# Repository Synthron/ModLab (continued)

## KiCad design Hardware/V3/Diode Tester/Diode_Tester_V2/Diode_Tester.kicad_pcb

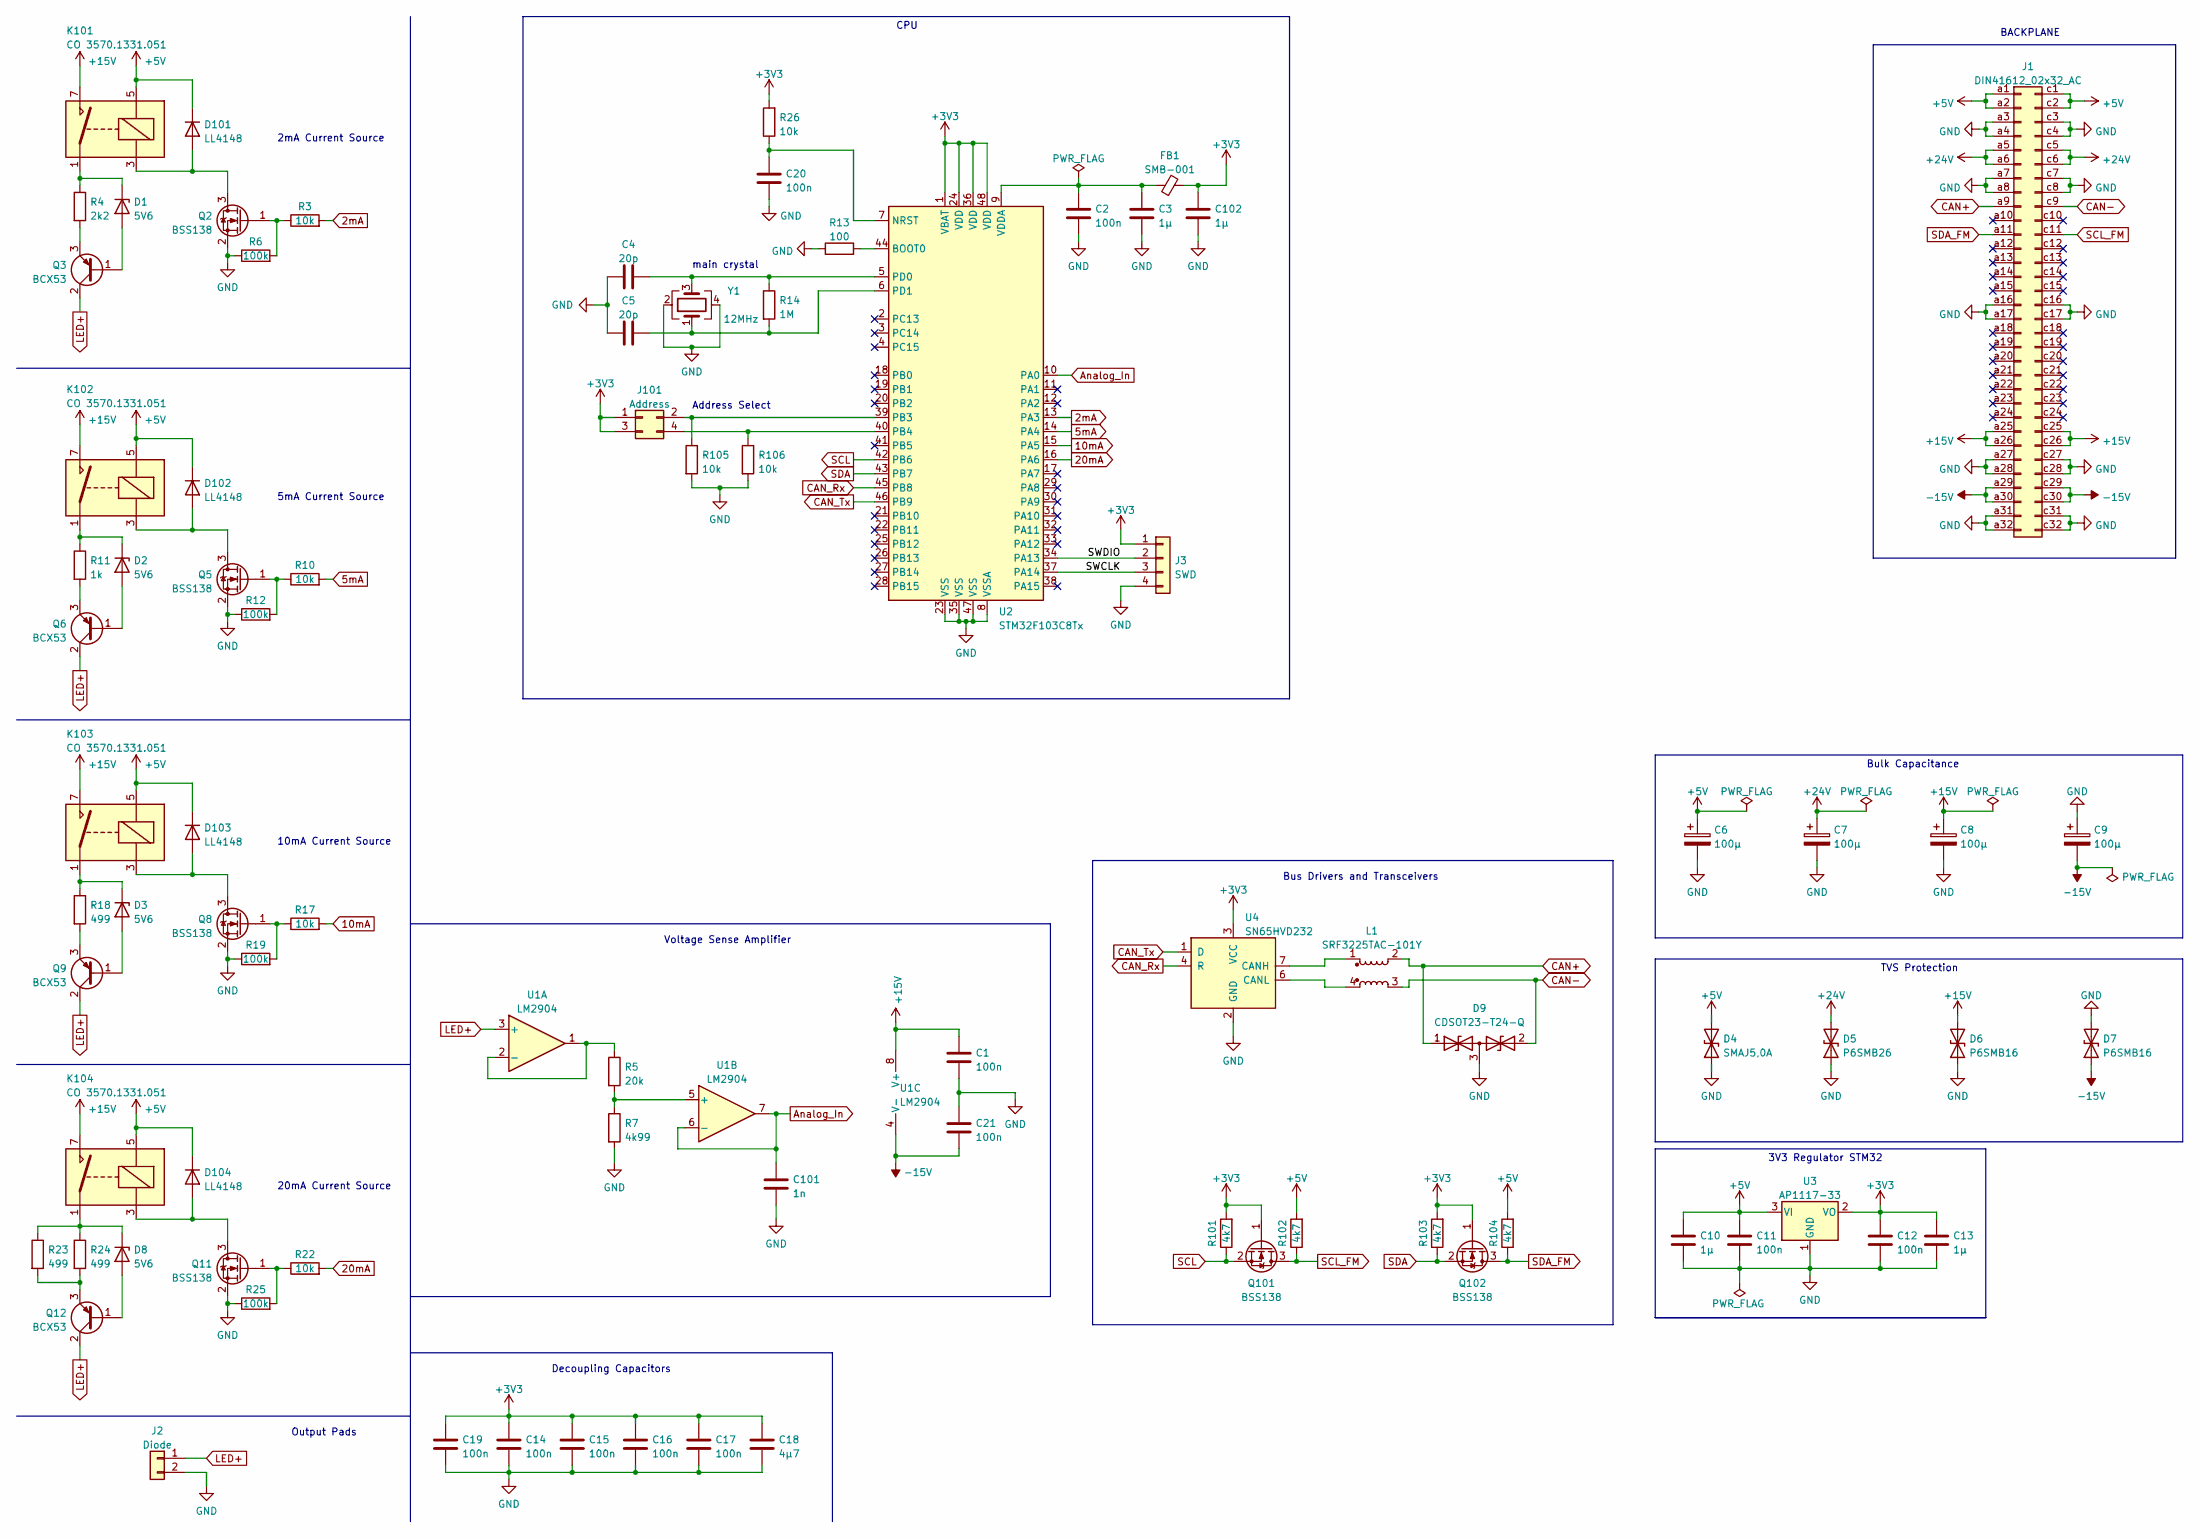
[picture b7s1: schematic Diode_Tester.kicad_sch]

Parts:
C1, C2, C11, C12, C14, C15, C16, C17, C19, C20, C21: 100n; C_0805_2012Metric
C3, C10, C13, C102: 1µ; C_0805_2012Metric
C4, C5: 20p; C_0805_2012Metric
C6, C7, C8, C9: 100µ; CP_Radial_D8.0mm_P5.00mm
C18: 4µ7; C_0805_2012Metric
C101: 1n; C_0805_2012Metric
D1, D2, D3, D8: 5V6; D_MiniMELF
D4: SMAJ5,0A; D_SMA
D5: P6SMB26; D_SMA
D6, D7: P6SMB16; D_SMA
D9: CDSOT23-T24-Q; SOT-23
D101, D102, D103, D104: LL4148; D_MiniMELF
FB1: SMB-001
J1: DIN41612_02x32_AC; VG64_Euro
J2: Diode; PinHeader_1x02_P2.54mm_Vertical
J3: SWD; JST_XH_B4B-XH-A_1x04_P2.50mm_Vertical
J101: Address; PinHeader_2x02_P2.54mm_Vertical
K101, K102, K103, K104: CO 3570.1331.051; Relay_SPST_StandexMeder_SIL_Form1A
L1: SRF3225TAC-101Y; SRF3225TAC
Q2, Q5, Q8, Q11, Q101, Q102: BSS138; SOT-23
Q3, Q6, Q9, Q12: BCX53; SOT-89-3
R3, R10, R17, R22, R26, R105, R106: 10k; R_0805_2012Metric
R4: 2k2; R_0805_2012Metric
R5: 20k; R_0805_2012Metric
R6, R12, R19, R25: 100k; R_0805_2012Metric
R7: 4k99; R_0805_2012Metric
R11: 1k; R_0805_2012Metric
R13: 100; R_0805_2012Metric
R14: 1M; R_0805_2012Metric
R18, R23, R24: 499; R_0805_2012Metric
R101, R102, R103, R104: 4k7; R_0805_2012Metric
U1: LM2904; SOIC-8_3.9x4.9mm_P1.27mm
U2: STM32F103C8Tx; LQFP-48_7x7mm_P0.5mm
U3: AP1117-33; SOT-223-3_TabPin2
U4: SN65HVD232; SOIC-8_3.9x4.9mm_P1.27mm
Y1: 12MHz; Crystal_SMD_5032-4Pin_5.0x3.2mm

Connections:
2mA: R3.2, U2.13 (PA3)
5mA: R10.2, U2.14 (PA4)
10mA: R17.2, U2.15 (PA5)
20mA: R22.2, U2.16 (PA6)
+3V3: C12.1, C13.1, C14.1, C15.1, C16.1, C17.1, C18.1, C19.1, C102.1, FB1.2, J3.1, J101.1, J101.3, Q101.1 (G), Q102.1 (G), R26.2, R101.2, R103.2, U2.1 (VBAT), U2.24 (VDD), U2.36 (VDD), U2.48 (VDD), U3.2 (VO), U4.3 (VCC)
+5V: C6.1, C10.1, C11.1, D4.2 (A2), D101.1 (K), D102.1 (K), D103.1 (K), D104.1 (K), J1.a1, J1.a2, J1.c1, J1.c2, K101.5, K102.5, K103.5, K104.5, R102.2, R104.2, U3.3 (VI)
+15V: C1.1, C8.1, D6.2 (A2), J1.a25, J1.a26, J1.c25, J1.c26, K101.7, K102.7, K103.7, K104.7, U1.8 (V+)
+24V: C7.1, D5.2 (A2), J1.a5, J1.a6, J1.c5, J1.c6
-15V: C9.2, C21.2, D7.1 (A1), J1.a29, J1.a30, J1.c29, J1.c30, U1.4 (V-)
/SWCLK: J3.3, U2.37 (PA14)
/SWDIO: J3.2, U2.34 (PA13)
Analog_In: C101.1, U1.6 (-), U1.7, U2.10 (PA0)
CAN+: D9.1 (A1), J1.a9, L1.2
CAN-: D9.2 (A2), J1.c9, L1.3
CAN_Rx: U2.45 (PB8), U4.4 (R)
CAN_Tx: U2.46 (PB9), U4.1 (D)
GND: C1.2, C2.2, C3.2, C4.1, C5.1, C6.2, C7.2, C8.2, C9.1, C10.2, C11.2, C12.2, C13.2, C14.2, C15.2, C16.2, C17.2, C18.2, C19.2, C20.2, C21.1, C101.2, C102.2, D4.1 (A1), D5.1 (A1), D6.1 (A1), D7.2 (A2), D9.3 (common), J1.a3, J1.a4, J1.a7, J1.a8, J1.a16, J1.a17, J1.a27, J1.a28, J1.a31, J1.a32, J1.c3, J1.c4, J1.c7, J1.c8, J1.c16, J1.c17, J1.c27, J1.c28, J1.c31, J1.c32, J2.2, J3.4, Q2.2 (S), Q5.2 (S), Q8.2 (S), Q11.2 (S), R6.1, R7.2, R12.1, R13.1, R19.1, R25.1, R105.2, R106.2, U2.8 (VSSA), U2.23 (VSS), U2.35 (VSS), U2.47 (VSS), U3.1 (GND), U4.2 (GND), Y1.2, Y1.4
LED+: J2.1, Q3.2 (C), Q6.2 (C), Q9.2 (C), Q12.2 (C), U1.3 (+)
unnamed: C2.1, C3.1, FB1.1, U2.9 (VDDA)
unnamed: C4.2, R14.1, U2.5 (PD0), Y1.3
unnamed: C5.2, R14.2, U2.6 (PD1), Y1.1
unnamed: C20.1, R26.1, U2.7 (NRST)
unnamed: D1.1 (K), K101.1, R4.1
unnamed: D1.2 (A), Q3.1 (B)
unnamed: D2.1 (K), K102.1, R11.1
unnamed: D2.2 (A), Q6.1 (B)
unnamed: D3.1 (K), K103.1, R18.1
unnamed: D3.2 (A), Q9.1 (B)
unnamed: D8.1 (K), K104.1, R23.1, R24.1
unnamed: D8.2 (A), Q12.1 (B)
unnamed: L1.1, U4.7 (CANH)
unnamed: L1.4, U4.6 (CANL)
unnamed: Q2.1 (G), R3.1, R6.2
unnamed: D101.2 (A), K101.3, Q2.3 (D)
unnamed: Q3.3 (E), R4.2
unnamed: Q5.1 (G), R10.1, R12.2
unnamed: D102.2 (A), K102.3, Q5.3 (D)
unnamed: Q6.3 (E), R11.2
unnamed: Q8.1 (G), R17.1, R19.2
unnamed: D103.2 (A), K103.3, Q8.3 (D)
unnamed: Q9.3 (E), R18.2
unnamed: Q11.1 (G), R22.1, R25.2
unnamed: D104.2 (A), K104.3, Q11.3 (D)
unnamed: Q12.3 (E), R23.2, R24.2
unnamed: R5.1, U1.1, U1.2 (-)
unnamed: R5.2, R7.1, U1.5 (+)
unnamed: R13.2, U2.44 (BOOT0)
unnamed: J101.2, R105.1, U2.39 (PB3)
unnamed: J101.4, R106.1, U2.40 (PB4)
SCL: Q101.2 (S), R101.1, U2.42 (PB6)
SCL_FM: J1.c11, Q101.3 (D), R102.1
SDA: Q102.2 (S), R103.1, U2.43 (PB7)
SDA_FM: J1.a11, Q102.3 (D), R104.1

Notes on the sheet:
2mA Current Source
10mA Current Source
Decoupling Capacitors
TVS Protection
3V3 Regulator STM32
Output Pads
main crystal
20mA Current Source
Address Select
CPU
BACKPLANE
Bus Drivers and Transceivers
Bulk Capacitance
5mA Current Source
Voltage Sense Amplifier

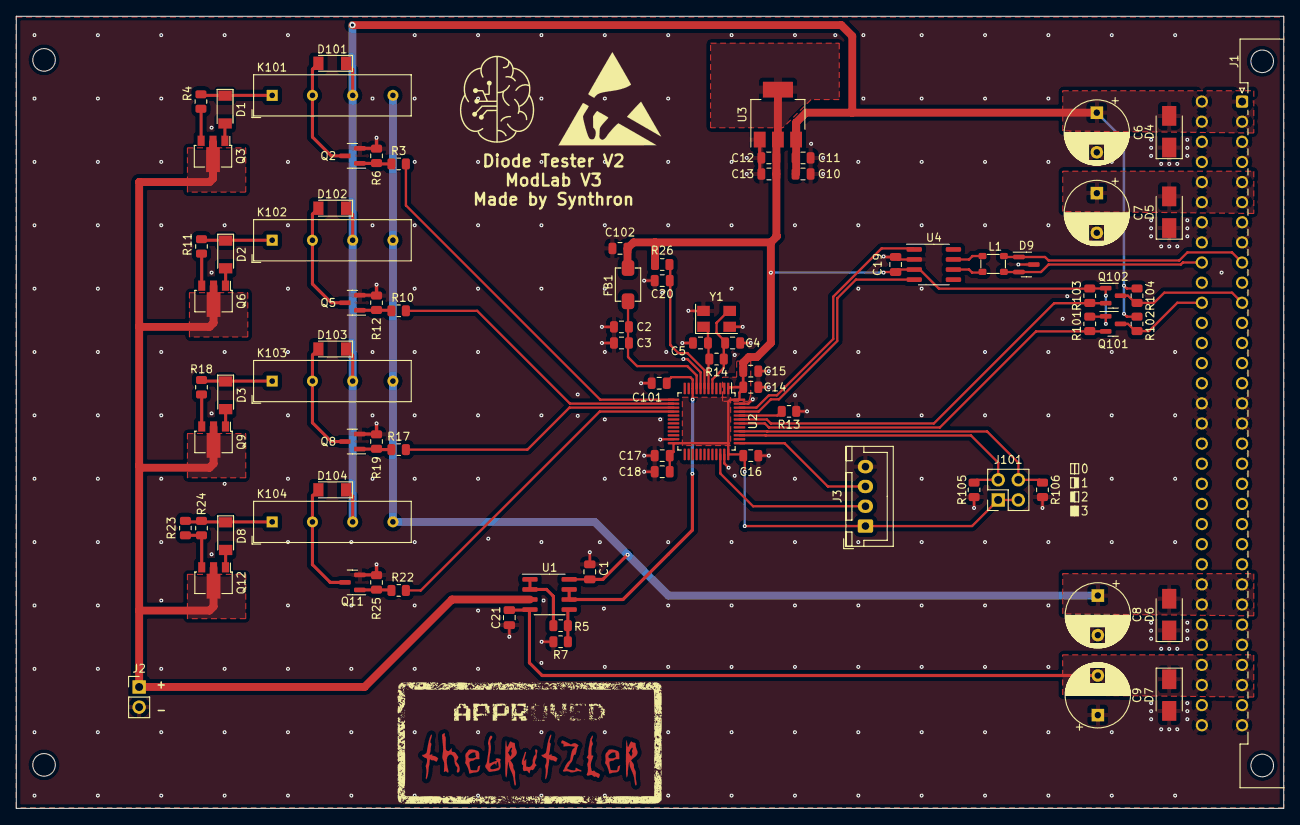
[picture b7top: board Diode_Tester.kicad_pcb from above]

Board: 2 copper layers, 160.0 x 100.0 mm, 85 parts (0 on the bottom side), 53 nets.

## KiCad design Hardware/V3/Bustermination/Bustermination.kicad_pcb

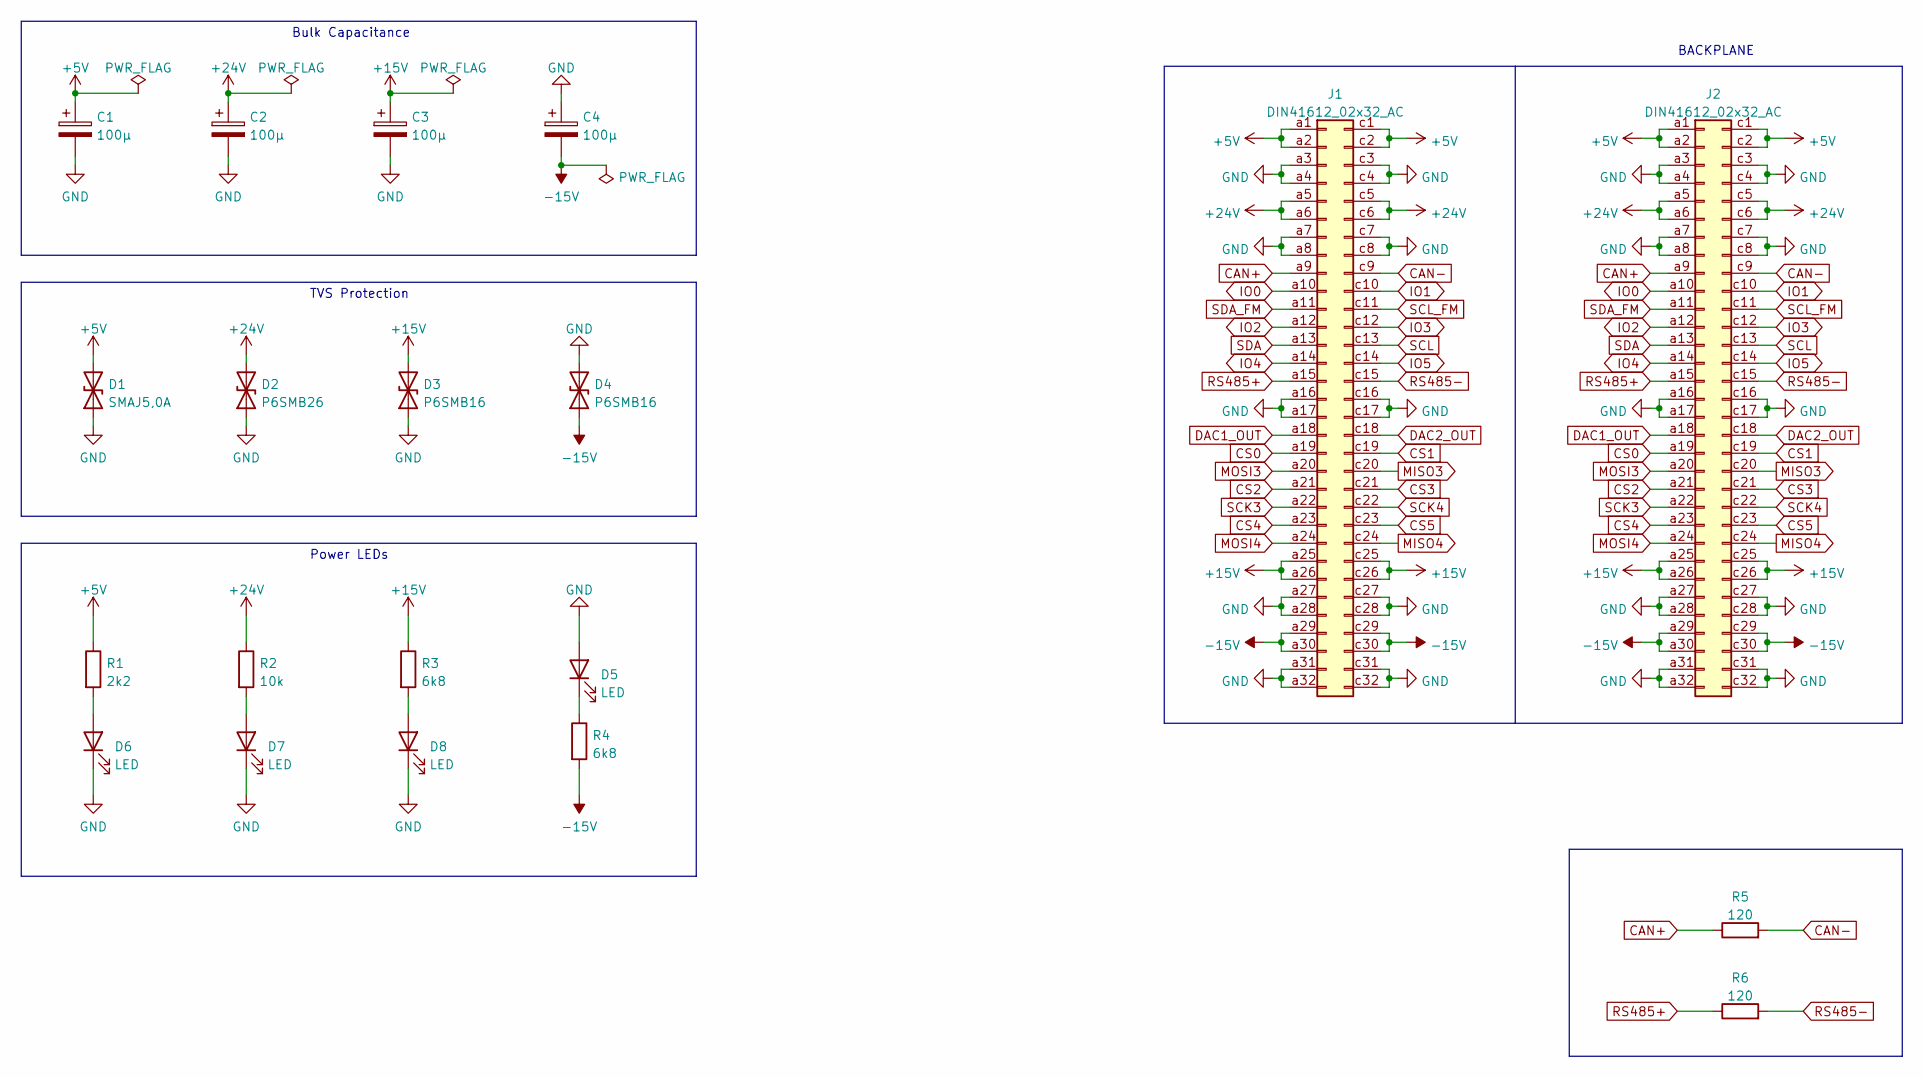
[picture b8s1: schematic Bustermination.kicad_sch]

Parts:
C1, C2, C3, C4: 100µ; CP_Radial_D8.0mm_P5.00mm
D1: SMAJ5,0A; D_SMA
D2: P6SMB26; D_SMA
D3, D4: P6SMB16; D_SMA
D5, D6, D7, D8: LED; LED_D3.0mm
J1: DIN41612_02x32_AC; DIN41612_C_2x32_Female_Vertical_THT
J2: DIN41612_02x32_AC; VG64_Euro
R1: 2k2; R_Axial_DIN0204_L3.6mm_D1.6mm_P7.62mm_Horizontal
R2: 10k; R_Axial_DIN0204_L3.6mm_D1.6mm_P7.62mm_Horizontal
R3, R4: 6k8; R_Axial_DIN0204_L3.6mm_D1.6mm_P7.62mm_Horizontal
R5, R6: 120; R_Axial_DIN0204_L3.6mm_D1.6mm_P7.62mm_Horizontal

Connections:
+5V: C1.1, D1.2 (A2), J1.a1, J1.a2, J1.c1, J1.c2, J2.a1, J2.a2, J2.c1, J2.c2, R1.1
+15V: C3.1, D3.2 (A2), J1.a25, J1.a26, J1.c25, J1.c26, J2.a25, J2.a26, J2.c25, J2.c26, R3.1
+24V: C2.1, D2.2 (A2), J1.a5, J1.a6, J1.c5, J1.c6, J2.a5, J2.a6, J2.c5, J2.c6, R2.1
-15V: C4.2, D4.1 (A1), J1.a29, J1.a30, J1.c29, J1.c30, J2.a29, J2.a30, J2.c29, J2.c30, R4.2
CAN+: J1.a9, J2.a9, R5.1
CAN-: J1.c9, J2.c9, R5.2
CS0: J1.a19, J2.a19
CS1: J1.c19, J2.c19
CS2: J1.a21, J2.a21
CS3: J1.c21, J2.c21
CS4: J1.a23, J2.a23
CS5: J1.c23, J2.c23
DAC1_OUT: J1.a18, J2.a18
DAC2_OUT: J1.c18, J2.c18
GND: C1.2, C2.2, C3.2, C4.1, D1.1 (A1), D2.1 (A1), D3.1 (A1), D4.2 (A2), D5.2 (A), D6.1 (K), D7.1 (K), D8.1 (K), J1.a3, J1.a4, J1.a7, J1.a8, J1.a16, J1.a17, J1.a27, J1.a28, J1.a31, J1.a32, J1.c3, J1.c4, J1.c7, J1.c8, J1.c16, J1.c17, J1.c27, J1.c28, J1.c31, J1.c32, J2.a3, J2.a4, J2.a7, J2.a8, J2.a16, J2.a17, J2.a27, J2.a28, J2.a31, J2.a32, J2.c3, J2.c4, J2.c7, J2.c8, J2.c16, J2.c17, J2.c27, J2.c28, J2.c31, J2.c32
IO0: J1.a10, J2.a10
IO1: J1.c10, J2.c10
IO2: J1.a12, J2.a12
IO3: J1.c12, J2.c12
IO4: J1.a14, J2.a14
IO5: J1.c14, J2.c14
MISO3: J1.c20, J2.c20
MISO4: J1.c24, J2.c24
MOSI3: J1.a20, J2.a20
MOSI4: J1.a24, J2.a24
unnamed: D5.1 (K), R4.1
unnamed: D6.2 (A), R1.2
unnamed: D7.2 (A), R2.2
unnamed: D8.2 (A), R3.2
RS485+: J1.a15, J2.a15, R6.1
RS485-: J1.c15, J2.c15, R6.2
SCK3: J1.a22, J2.a22
SCK4: J1.c22, J2.c22
SCL: J1.c13, J2.c13
SCL_FM: J1.c11, J2.c11
SDA: J1.a13, J2.a13
SDA_FM: J1.a11, J2.a11

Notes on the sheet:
TVS Protection
Power LEDs
BACKPLANE
Bulk Capacitance

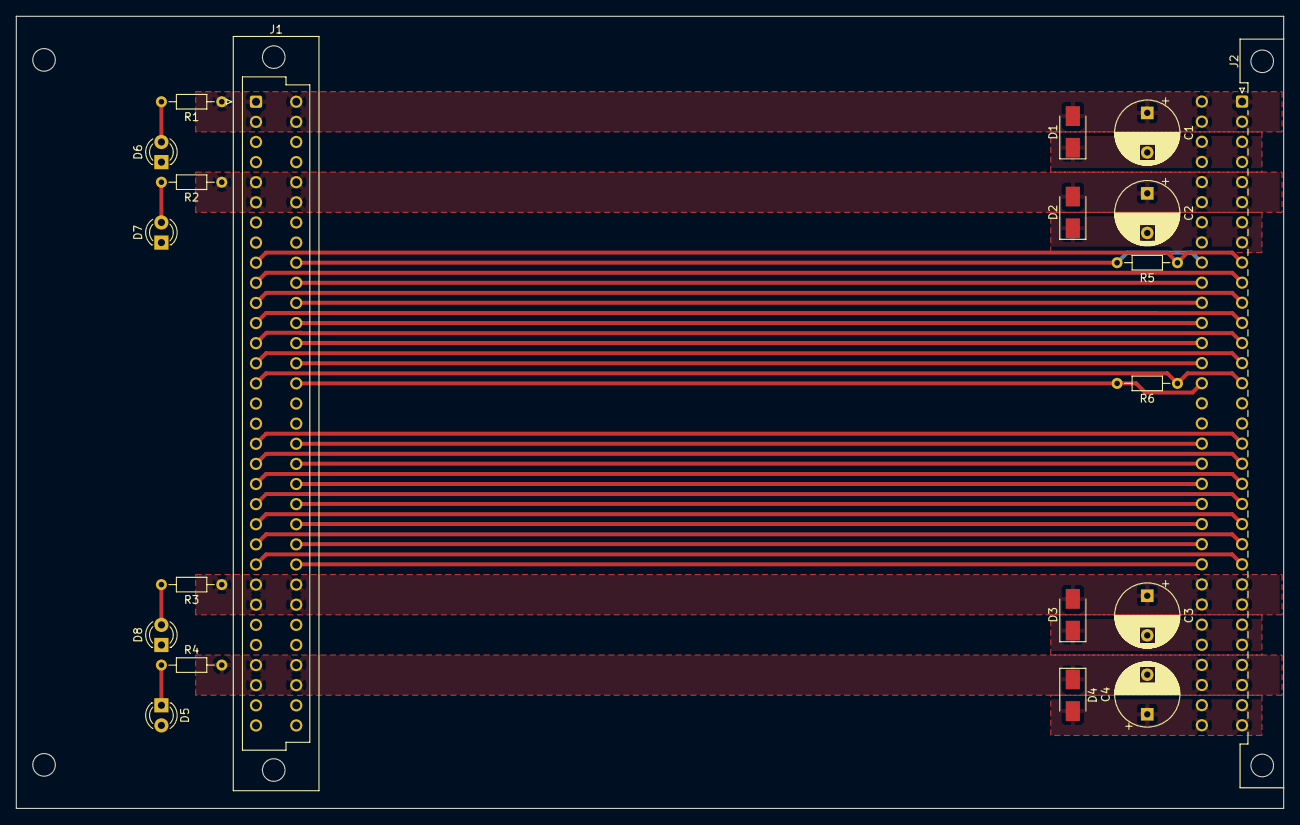
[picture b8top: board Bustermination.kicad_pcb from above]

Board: 2 copper layers, 160.0 x 100.0 mm, 20 parts (0 on the bottom side), 37 nets.

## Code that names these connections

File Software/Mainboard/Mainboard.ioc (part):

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Mcu.Name=STM32F407V(E-G)Tx
Mcu.Package=LQFP100
Mcu.UserName=STM32F407VGTx
PA0-WKUP.Mode=Asynchronous
PA0-WKUP.Signal=UART4_TX
PA1.Mode=Asynchronous
PA1.Signal=UART4_RX
PA10.GPIOParameters=GPIO_Label
PA10.GPIO_Label=USB_Disconnect
PA10.Signal=GPIO_Output
PA11.Mode=Device_Only
PA11.Signal=USB_OTG_FS_DM
PA12.Mode=Device_Only
PA12.Signal=USB_OTG_FS_DP
PA13.Mode=Serial_Wire
PA13.Signal=SYS_JTMS-SWDIO
PA14.Mode=Serial_Wire
PA14.Signal=SYS_JTCK-SWCLK
PA2.GPIOParameters=GPIO_Label
PA2.GPIO_Label=RS485_DIR
PA2.Signal=GPIO_Output
PA3.GPIOParameters=GPIO_Label
PA3.GPIO_Label=ESP_CS
PA3.Signal=GPIO_Output
PA4.Signal=COMP_DAC1_group
PA5.Signal=COMP_DAC2_group
PA6.Mode=Full_Duplex_Master
PA6.Signal=SPI1_MISO
PA7.Mode=Full_Duplex_Master
PA7.Signal=SPI1_MOSI
PA9.Mode=Asynchronous
PA9.Signal=USART1_TX
PB0.GPIOParameters=GPIO_Label
PB0.GPIO_Label=SD_DETECT
PB0.Signal=GPIO_Input
PB1.GPIOParameters=GPIO_Label
PB1.GPIO_Label=SD_PROTECT
PB1.Signal=GPIO_Input
PB10.Mode=I2C
PB10.Signal=I2C2_SCL
PB11.Mode=I2C
PB11.Signal=I2C2_SDA
PB13.Mode=Full_Duplex_Master
PB13.Signal=SPI2_SCK
PB3.Mode=Full_Duplex_Master
PB3.Signal=SPI1_SCK
PB5.Mode=Full_Duplex_Master
PB5.Signal=SPI3_MOSI
PB6.Mode=I2C
PB6.Signal=I2C1_SCL
PB7.Mode=Asynchronous
PB7.Signal=USART1_RX
PB9.Mode=I2C
PB9.Signal=I2C1_SDA
PC0.GPIOParameters=GPIO_Label
PC0.GPIO_Label=ESP_RDY
PC0.Signal=GPIO_Input
PC1.GPIOParameters=GPIO_Label
PC1.GPIO_Label=ESP_CS
PC1.Signal=GPIO_Output
PC10.Mode=Full_Duplex_Master
PC10.Signal=SPI3_SCK
PC11.Mode=Full_Duplex_Master
PC11.Signal=SPI3_MISO
PC12.Mode=SD_1_bit
PC12.Signal=SDIO_CK
PC14-OSC32_IN.Mode=LSE-External-Oscillator
PC14-OSC32_IN.Signal=RCC_OSC32_IN
PC15-OSC32_OUT.Mode=LSE-External-Oscillator
PC15-OSC32_OUT.Signal=RCC_OSC32_OUT
PC2.Mode=Full_Duplex_Master
PC2.Signal=SPI2_MISO
PC3.Mode=Full_Duplex_Master
PC3.Signal=SPI2_MOSI
PC8.Mode=SD_1_bit
PC8.Signal=SDIO_D0
PD0.Mode=CAN_Activate
PD0.Signal=CAN1_RX
PD1.Mode=CAN_Activate
PD1.Signal=CAN1_TX
PD10.GPIOParameters=GPIO_Label
PD10.GPIO_Label=IO_0
PD10.Signal=GPIO_Output
PD11.GPIOParameters=GPIO_Label
PD11.GPIO_Label=IO_1
PD11.Signal=GPIO_Output
PD12.GPIOParameters=GPIO_Label
PD12.GPIO_Label=IO_2
PD12.Signal=GPIO_Output
PD13.GPIOParameters=GPIO_Label
PD13.GPIO_Label=IO_3
PD13.Signal=GPIO_Output
PD14.GPIOParameters=GPIO_Label
PD14.GPIO_Label=IO_4
PD14.Signal=GPIO_Output
PD15.GPIOParameters=GPIO_Label
PD15.GPIO_Label=IO_5
PD15.Signal=GPIO_Output
PD2.Mode=SD_1_bit
PD2.Signal=SDIO_CMD
PE0.GPIOParameters=GPIO_Label
PE0.GPIO_Label=LED_USB
PE0.Signal=GPIO_Output
PE1.GPIOParameters=GPIO_Label
PE1.GPIO_Label=LED_ESP
PE1.Signal=GPIO_Output
PE10.GPIOParameters=GPIO_Label
PE10.GPIO_Label=CS0
PE10.Signal=GPIO_Output
PE11.GPIOParameters=GPIO_Label
PE11.GPIO_Label=CS1
PE11.Signal=GPIO_Output
PE12.GPIOParameters=GPIO_Label
PE12.GPIO_Label=CS2
PE12.Signal=GPIO_Output
PE13.GPIOParameters=GPIO_Label
PE13.GPIO_Label=CS3
PE13.Signal=GPIO_Output
PE14.GPIOParameters=GPIO_Label
PE14.GPIO_Label=CS4
PE14.Signal=GPIO_Output
PE15.GPIOParameters=GPIO_Label
PE15.GPIO_Label=CS5
PE15.Signal=GPIO_Output
PE2.GPIOParameters=GPIO_Label
PE2.GPIO_Label=LED_SPI
PE2.Signal=GPIO_Output
PE3.GPIOParameters=GPIO_Label
PE3.GPIO_Label=LED_I2C
PE3.Signal=GPIO_Output
PE4.GPIOParameters=GPIO_Label
PE4.GPIO_Label=LED_SD
PE4.Signal=GPIO_Output
PE5.GPIOParameters=GPIO_Label
PE5.GPIO_Label=LED_CAN
PE5.Signal=GPIO_Output
PE6.GPIOParameters=GPIO_Label
PE6.GPIO_Label=LED_TFT
PE6.Signal=GPIO_Output
PE7.GPIOParameters=GPIO_Label
PE7.GPIO_Label=LED_485
PE7.Signal=GPIO_Output
PH0-OSC_IN.Mode=HSE-External-Oscillator
PH0-OSC_IN.Signal=RCC_OSC_IN
PH1-OSC_OUT.Mode=HSE-External-Oscillator
PH1-OSC_OUT.Signal=RCC_OSC_OUT
RCC.HSE_VALUE=8000000
RCC.SYSCLKFreq_VALUE=168000000
RCC.SYSCLKSource=RCC_SYSCLKSOURCE_PLLCLK
board=custom

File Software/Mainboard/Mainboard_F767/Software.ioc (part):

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Mcu.Name=STM32F767ZITx
Mcu.Package=LQFP144
Mcu.UserName=STM32F767ZITx
PA0/WKUP.GPIOParameters=GPIO_Label
PA0/WKUP.GPIO_Label=SD_Detect
PA0/WKUP.Signal=GPIO_Input
PA1.GPIOParameters=GPIO_Label
PA1.GPIO_Label=SD_Protect
PA1.Signal=GPIO_Input
PA10.GPIOParameters=GPIO_Label
PA10.GPIO_Label=USB_Disconnect
PA10.Signal=GPIO_Output
PA11.Mode=Device_Only
PA11.Signal=USB_OTG_FS_DM
PA12.Mode=Device_Only
PA12.Signal=USB_OTG_FS_DP
PA13.Mode=Serial_Wire
PA13.Signal=SYS_JTMS-SWDIO
PA14.Mode=Serial_Wire
PA14.Signal=SYS_JTCK-SWCLK
PA15.GPIOParameters=GPIO_Label
PA15.GPIO_Label=CS_2
PA15.Signal=GPIO_Output
PA2.GPIOParameters=GPIO_Label
PA2.GPIO_Label=ESP_RDY
PA2.Signal=GPXTI2
PA3.GPIOParameters=GPIO_Label
PA3.GPIO_Label=ESP_CS
PA3.Signal=GPIO_Output
PA4.Signal=COMP_DAC1_group
PA5.Signal=COMP_DAC2_group
PA6.Mode=Full_Duplex_Master
PA6.Signal=SPI1_MISO
PA7.Mode=Full_Duplex_Master
PA7.Signal=SPI1_MOSI
PA8.GPIOParameters=GPIO_Label
PA8.GPIO_Label=CS_0
PA8.Signal=GPIO_Output
PA9.GPIOParameters=GPIO_Label
PA9.GPIO_Label=CS_1
PA9.Signal=GPIO_Output
PB0.GPIOParameters=GPIO_Label
PB0.GPIO_Label=CS_3
PB0.Signal=GPIO_Output
PB1.GPIOParameters=GPIO_Label
PB1.GPIO_Label=CS_4
PB1.Signal=GPIO_Output
PB10.Mode=I2C
PB10.Signal=I2C2_SCL
PB11.Mode=I2C
PB11.Signal=I2C2_SDA
PB12.GPIOParameters=GPIO_Label
PB12.GPIO_Label=GPIO_0
PB12.Signal=GPIO_Input
PB13.Mode=Full_Duplex_Master
PB13.Signal=SPI2_SCK
PB14.Mode=Asynchronous
PB14.Signal=USART1_TX
PB15.Mode=Asynchronous
PB15.Signal=USART1_RX
PB2.Mode=Full_Duplex_Master
PB2.Signal=SPI3_MOSI
PB3.Mode=Full_Duplex_Master
PB3.Signal=SPI3_SCK
PB4.Mode=Full_Duplex_Master
PB4.Signal=SPI3_MISO
PB5.GPIOParameters=GPIO_Label
PB5.GPIO_Label=CS_5
PB5.Signal=GPIO_Output
PB6.Mode=I2C
PB6.Signal=I2C1_SCL
PB7.Mode=I2C
PB7.Signal=I2C1_SDA
PB8.Mode=CAN_Activate
PB8.Signal=CAN1_RX
PB9.Mode=CAN_Activate
PB9.Signal=CAN1_TX
PC0.GPIOParameters=GPIO_Label
PC0.GPIO_Label=GPIO_1
PC0.Signal=GPIO_Input
PC1.Mode=Full_Duplex_Master
PC1.Signal=SPI2_MOSI
PC10.Mode=SD_4_bits_Wide_bus
PC10.Signal=SDMMC1_D2
PC11.Mode=SD_4_bits_Wide_bus
PC11.Signal=SDMMC1_D3
PC12.Mode=SD_4_bits_Wide_bus
PC12.Signal=SDMMC1_CK
PC2.Mode=Full_Duplex_Master
PC2.Signal=SPI2_MISO
PC3.GPIOParameters=GPIO_Label
PC3.GPIO_Label=GPIO_2
PC3.Signal=GPIO_Input
PC4.GPIOParameters=GPIO_Label
PC4.GPIO_Label=GPIO_3
PC4.Signal=GPIO_Input
PC5.GPIOParameters=GPIO_Label
PC5.GPIO_Label=GPIO_4
PC5.Signal=GPIO_Input
PC6.GPIOParameters=GPIO_Label
PC6.GPIO_Label=GPIO_5
PC6.Signal=GPIO_Input
PC7.Mode=NorPsramChipSelect1_1
PC7.Signal=FMC_NE1
PC8.Mode=SD_4_bits_Wide_bus
PC8.Signal=SDMMC1_D0
PC9.Mode=SD_4_bits_Wide_bus
PC9.Signal=SDMMC1_D1
PD0.Signal=FMC_D2_DA2
PD1.Signal=FMC_D3_DA3
PD10.Signal=FMC_D15_DA15
PD11.Signal=FMC_A16_CLE
PD12.Signal=FMC_A17_ALE
PD13.Signal=FMC_A18
PD14.Signal=FMC_D0_DA0
PD15.Signal=FMC_D1_DA1
PD2.Mode=SD_4_bits_Wide_bus
PD2.Signal=SDMMC1_CMD
PD3.GPIOParameters=PinState,GPIO_Label
PD3.GPIO_Label=LCD_CS
PD3.PinState=GPIO_PIN_SET
PD3.Signal=GPIO_Output
PD4.Signal=FMC_NOE
PD5.Signal=FMC_NWE
PD8.Signal=FMC_D13_DA13
PD9.Signal=FMC_D14_DA14
PE0.Signal=FMC_NBL0
PE1.Signal=FMC_NBL1
PE10.Signal=FMC_D7_DA7
PE11.Signal=FMC_D8_DA8
PE12.Signal=FMC_D9_DA9
PE13.Signal=FMC_D10_DA10
PE14.Signal=FMC_D11_DA11
PE15.Signal=FMC_D12_DA12
PE2.Mode=Full_Duplex_Master
PE2.Signal=SPI4_SCK
PE5.Mode=Full_Duplex_Master
PE5.Signal=SPI4_MISO
PE6.Mode=Full_Duplex_Master
PE6.Signal=SPI4_MOSI
PE7.Signal=FMC_D4_DA4
PE8.Signal=FMC_D5_DA5
PE9.Signal=FMC_D6_DA6
PF0.Signal=FMC_A0
PF1.Signal=FMC_A1
PF12.Signal=FMC_A6
PF13.Signal=FMC_A7
PF14.Signal=FMC_A8
PF15.Signal=FMC_A9
PF2.Signal=FMC_A2
PF3.Signal=FMC_A3
PF4.Signal=FMC_A4
PF5.Signal=FMC_A5
PF6.Mode=Asynchronous
PF6.Signal=UART7_RX
PF7.Mode=Asynchronous
PF7.Signal=UART7_TX
PF8.Mode=Hardware Flow Control (RS485)
PF8.Signal=UART7_DE
PG0.Signal=FMC_A10
PG1.Signal=FMC_A11
PG10.GPIOParameters=GPIO_Label
PG10.GPIO_Label=LED_I2C2
PG10.Signal=GPIO_Output
PG11.Mode=Full_Duplex_Master
PG11.Signal=SPI1_SCK
PG12.GPIOParameters=GPIO_Label
PG12.GPIO_Label=LED_ESP
PG12.Signal=GPIO_Output
PG13.GPIOParameters=GPIO_Label
PG13.GPIO_Label=LED_SD
PG13.Signal=GPIO_Output
PG14.GPIOParameters=GPIO_Label
PG14.GPIO_Label=LED_SPI3
PG14.Signal=GPIO_Output
PG15.GPIOParameters=GPIO_Label
PG15.GPIO_Label=LED_SPI4
PG15.Signal=GPIO_Output
PG2.Signal=FMC_A12
PG3.Signal=FMC_A13
PG4.Signal=FMC_A14_BA0
PG5.Signal=FMC_A15_BA1
PG6.GPIOParameters=GPIO_Label
PG6.GPIO_Label=LED_CAN
PG6.Signal=GPIO_Output
PG7.GPIOParameters=GPIO_Label
PG7.GPIO_Label=LED_485
PG7.Signal=GPIO_Output
PG8.GPIOParameters=GPIO_Label
PG8.GPIO_Label=LED_I2C1
PG8.Signal=GPIO_Output
PG9.Mode=NorPsramChipSelect2_2
PG9.Signal=FMC_NE2
PH0/OSC_IN.Mode=HSE-External-Oscillator
PH0/OSC_IN.Signal=RCC_OSC_IN
PH1/OSC_OUT.Mode=HSE-External-Oscillator
PH1/OSC_OUT.Signal=RCC_OSC_OUT
RCC.HSE_VALUE=12000000
RCC.SYSCLKFreq_VALUE=216000000
RCC.SYSCLKSource=RCC_SYSCLKSOURCE_PLLCLK
board=custom

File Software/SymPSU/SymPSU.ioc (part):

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Mcu.Name=STM32F103C(8-B)Tx
Mcu.Package=LQFP48
Mcu.UserName=STM32F103C8Tx
PA0-WKUP.Signal=ADCx_IN0
PA1.Signal=ADCx_IN1
PA13.Mode=Serial_Wire
PA13.Signal=SYS_JTMS-SWDIO
PA14.Mode=Serial_Wire
PA14.Signal=SYS_JTCK-SWCLK
PA15.Signal=S_TIM2_CH1_ETR
PA2.Signal=ADCx_IN2
PA3.Signal=ADCx_IN3
PA7.GPIOParameters=GPIO_Label
PA7.GPIO_Label=Out_EN
PA7.Signal=GPIO_Output
PB10.Signal=S_TIM2_CH3
PB11.Signal=S_TIM2_CH4
PB2.GPIOParameters=GPIO_Label
PB2.GPIO_Label=ADD0
PB2.Signal=GPIO_Input
PB3.Signal=S_TIM2_CH2
PB4.GPIOParameters=GPIO_Label
PB4.GPIO_Label=ADD1
PB4.Signal=GPIO_Input
PB6.Mode=I2C
PB6.Signal=I2C1_SCL
PB7.Mode=I2C
PB7.Signal=I2C1_SDA
PB8.Mode=CAN_Activate
PB8.Signal=CAN_RX
PB9.Mode=CAN_Activate
PB9.Signal=CAN_TX
PD0-OSC_IN.Mode=HSE-External-Oscillator
PD0-OSC_IN.Signal=RCC_OSC_IN
PD1-OSC_OUT.Mode=HSE-External-Oscillator
PD1-OSC_OUT.Signal=RCC_OSC_OUT
RCC.HSE_VALUE=12000000
RCC.SYSCLKFreq_VALUE=72000000
RCC.SYSCLKSource=RCC_SYSCLKSOURCE_PLLCLK
board=custom

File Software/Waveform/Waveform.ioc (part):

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Mcu.Name=STM32F103C(8-B)Tx
Mcu.Package=LQFP48
Mcu.UserName=STM32F103C8Tx
PA0-WKUP.Signal=S_TIM2_CH1_ETR
PA1.Signal=S_TIM2_CH2
PA13.Mode=Serial_Wire
PA13.Signal=SYS_JTMS-SWDIO
PA14.Mode=Serial_Wire
PA14.Signal=SYS_JTCK-SWCLK
PA2.GPIOParameters=GPIO_Label
PA2.GPIO_Label=PWM_Out
PA2.Signal=GPIO_Output
PA4.GPIOParameters=GPIO_Label
PA4.GPIO_Label=OUT_Relais
PA4.Signal=GPIO_Output
PA5.Mode=TX_Only_Simplex_Unidirect_Master
PA5.Signal=SPI1_SCK
PA6.GPIOParameters=GPIO_Label
PA6.GPIO_Label=FSYNC
PA6.Signal=GPIO_Output
PA7.Mode=TX_Only_Simplex_Unidirect_Master
PA7.Signal=SPI1_MOSI
PB6.Mode=I2C
PB6.Signal=I2C1_SCL
PB7.Mode=I2C
PB7.Signal=I2C1_SDA
PB8.Mode=CAN_Activate
PB8.Signal=CAN_RX
PB9.Mode=CAN_Activate
PB9.Signal=CAN_TX
PD0-OSC_IN.Mode=HSE-External-Oscillator
PD0-OSC_IN.Signal=RCC_OSC_IN
PD1-OSC_OUT.Mode=HSE-External-Oscillator
PD1-OSC_OUT.Signal=RCC_OSC_OUT
RCC.HSE_VALUE=12000000
RCC.SYSCLKFreq_VALUE=72000000
RCC.SYSCLKSource=RCC_SYSCLKSOURCE_PLLCLK
board=custom

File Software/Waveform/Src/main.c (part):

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uint8_t setfreq = 0;

uint8_t waveform = wave_square;
uint16_t gain  = 0;
int16_t offset = 0;
uint32_t freq = 0;

// https://controllerstech.com/can-protocol-in-stm32/
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  address = ADDR_WaveGen | (HAL_GPIO_ReadPin(GPIOB, GPIO_PIN_4)) | (HAL_GPIO_ReadPin(GPIOB, GPIO_PIN_3) << 1);


  HAL_GPIO_WritePin(OUT_Relais_GPIO_Port, OUT_Relais_Pin, 0);

  HAL_TIM_PWM_Start(&htim2, TIM_CHANNEL_1); // GAIN
  HAL_TIM_PWM_Start(&htim2, TIM_CHANNEL_2); // OFFSET
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  /* USER CODE BEGIN WHILE */
  while (1)
  {
    HAL_GPIO_WritePin(OUT_Relais_GPIO_Port, OUT_Relais_Pin, outputState);
    if(setfreq)
    {
      setfreq = 0;
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
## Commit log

2023-03-02 Removed History due to issues
2023-03-05 Edit Mainboard IOC for Nextion Display Implement first Nextion Display Code start tft library for nextion display
2023-03-06 TFT Update Implementing general TFT functions Implementing module loops Implementing more functionality slight documentation update regarding TFT
2023-03-07 bugfuxes
2023-03-13 start work on Electronic Load
2023-03-14 finalize electronic load; Readme Update
2023-03-28 Load update
2023-04-02 Code Update IOC-File updates Base Code Generation Small Doc and Readme Update
2023-04-11 Code Update
2023-04-16 Waveform Gen Initial code Porting AD9833 Library Readme Update
2023-04-18 Code Update Implement full code for Waveform Generator Small doc update Readme Update
2023-04-19 Code Fix for Mainboard
2023-04-24 SMPS Schematic and PCB Bugfix
2023-04-30 PCB Update
2023-06-11 GPN Update Bugfixes on Function Generator New code for SymPSU
2024-03-05 Add V2 Mainboard
2024-05-28 TFT Code Update
2024-06-03 GPN Update Port over Mainboard Code to F407
